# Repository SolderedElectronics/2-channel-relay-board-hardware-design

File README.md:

# 2-channel relay board Hardware Design

## About the Product

|  |
| :----------------------------------------------------------: |
| [Buy 2-channel relay board](https://www.solde.red/333023) |

Did you ever wanted to turn on and off a device that needs large current or voltage? Whether operating on DC or AC, a relay is what you need. A relay is actually an electronic switch that is activated by a signal we send from a Dasduino or Arduino. This module further simplifies the whole process because it contains everything you need for the relay to work, and you just have to connect it to the microcontroller and power supply. You don’t have to think about voltages and currents, insulation between high and low voltage or grounding, everything is already taken care of on the board. This product has 2 relays.

---

## Repository Contents

This repository contains all design files for 2-channel relay board, organized as follows:

- **`CAD` folder**: Contains KiCAD design files, including:
  - Schematics
  - PCB layout
  - Panel PCB layout
  - Source 3D files in Fusion360, if any
  - All files are sorted by version with a detailed change log.
- **`OUTPUTS` folder**: Includes all production-ready files, such as:
  - Bill of Materials (BOM) and interactive BOM (iBOM)
  - PDF versions of schematics
  - 3D `.step` file of the board
  - 3D-printable models
  - Gerber files for PCB manufacturing
  - Image of the pinout of the board
  - Product image
  - Compliance, legal and generic sales documents

Refer to the `Change Log` in the CAD folder for details about updates between versions.

---

## Learn More About the Product

Beyond the repository, explore the following resources:

### Soldered Verify

The **Soldered Verify** system ensures every board you purchase from Soldered is fully functional. It also provides access to exclusive test data for your product. To get started, find the unique Soldered Verify ID on your product's packaging and enter the ID on the [Soldered Verify page](https://soldered.com/verify/) to access test results and additional product details.

### Soldered Community

Soldered Community is your go-to place for technical support. Our engineers track and answer all questions posted there, and it’s a great space for the maker community. Get answers to your questions and solutions for your challenges at [Soldered Community](https://soldered.com/community).

### solde.red

solde.red is an ultimate URL shortener and information hub. Access it by typing solde.red/ followed by your product SKU, e.g., [solde.red/333000](https://solde.red/333000), to find getting-started guides, datasheets, open-source hardware and software files, certifications, images, pinouts, and more. Read more about the shortener [here](https://solde.red/info/).

---

## Contributing

Contributions are welcome! Here’s how you can get involved:

- Submit pull requests to enhance the design or fix issues.
- Report bugs or problems by opening an issue.

We encourage community collaboration to make this product even better.

---

## About Soldered

[Soldered for Makers](https://soldered.com) specializes in designing and manufacturing electronic products tailored for enthusiasts, ranging from hobbyists to professionals. Our portfolio includes electronic boards, sensors, and actuators that are widely utilized in fields such as microelectronics, mechatronics, robotics, programming, and IoT. Every product we offer is designed in-house and built upon open-source hardware and software platforms. Proudly certified and manufactured within the European Union, our catalog likely includes the product you need for your project.

We complement these products with comprehensive tutorials and manuals, product descriptions, schematics, programming codes, and project examples. Our round-the-clock [customer and technical support](https://soldered.com/community) is available for all our products, irrespective of the sales channel. Soldered’s success and services reflect our maker community’s unwavering [trust](https://www.trustpilot.com/review/soldered.com), for which we are deeply grateful. Join our community and create using Soldered products.

---

## License

All Soldered open-source hardware (OSH) is under The TAPR Open Hardware License. Read more in the LICENSE file located in this repository.

**Disclaimer:**

No warranty - all designs in this repository are distributed in the hope that they will be useful, but without any warranty. They are provided "AS IS", therefore without warranty of any kind, either expressed or implied. The entire quality and performance of what you do with the contents of this repository are your responsibility. In no event Soldered Electronics will be liable for your damages, or losses, including any general, special, incidental, or consequential damage arising out of the use or inability to use the contents of this repository. 

---

## Have fun!

Thank you for your support from your fellow makers at Soldered Electronics.

Happy Making!

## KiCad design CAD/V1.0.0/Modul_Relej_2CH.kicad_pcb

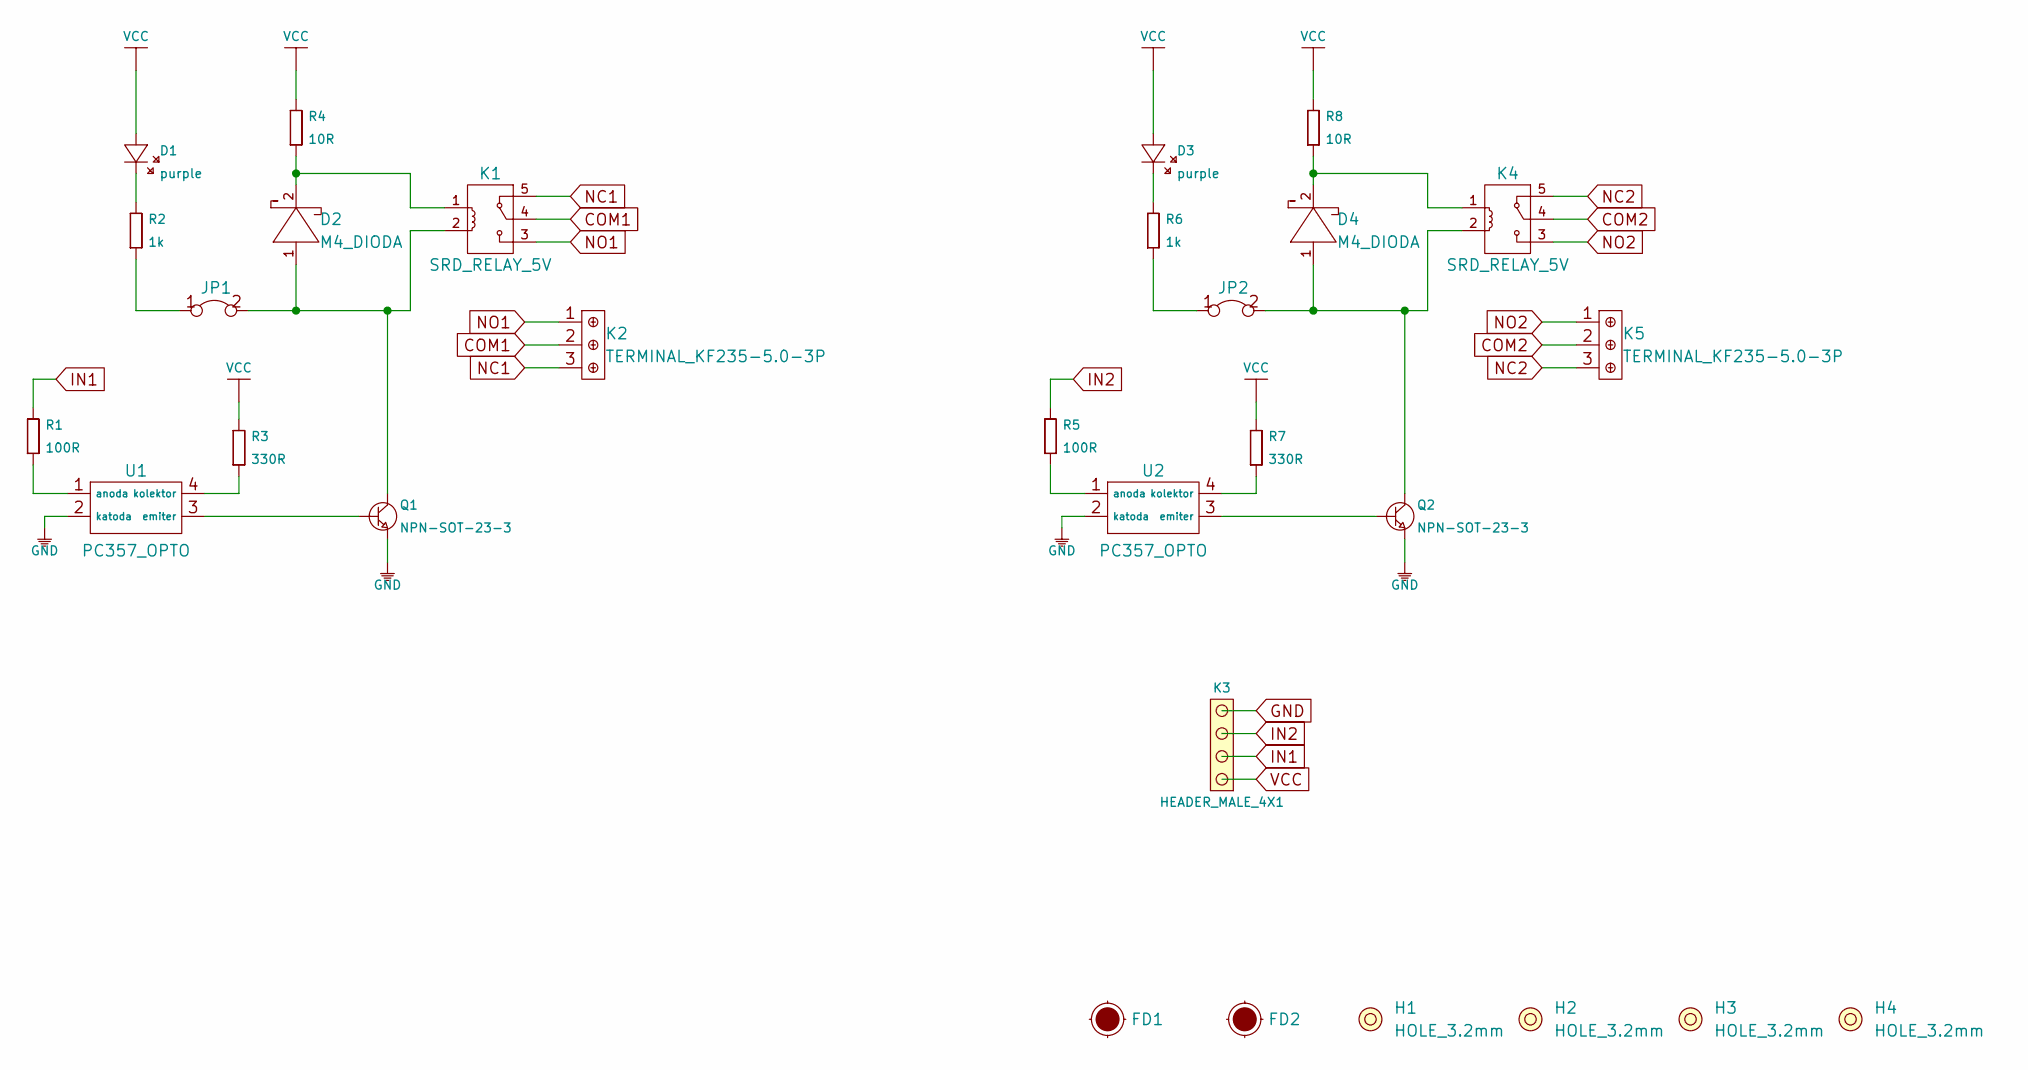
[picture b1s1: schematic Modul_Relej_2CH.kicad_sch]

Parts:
D1, D3: purple; 0402LED
D2, D4: M4_DIODA
FD1, FD2: Fiducial_Stencil; FIDUCIAL_1MM_PASTE
H1, H2, H3, H4: HOLE_3.2mm
JP1, JP2: SMD-JUMPER-CONNECTED_TRACE_NOSLODERMASK
K1, K4: SRD_RELAY_5V
K2, K5: TERMINAL_KF235-5.0-3P
K3: HEADER_MALE_4X1
Q1, Q2: NPN-SOT-23-3; SOT-23-3
R1, R5: 100R; 0603R
R2, R6: 1k; 0402R
R3, R7: 330R; 0603R
R4, R8: 10R; 0603R
U1, U2: PC357_OPTO

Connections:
COM1: K1.4, K2.2
COM2: K4.4, K5.2
GND: K3.4, Q1.2 (E), Q2.2 (E), U1.2 (katoda), U2.2 (katoda)
IN1: K3.2, R1.2
IN2: K3.3, R5.2
NC1: K1.5, K2.3
NC2: K4.5, K5.3
NO1: K1.3, K2.1
NO2: K4.3, K5.1
unnamed: D1.2 (K), R2.2
unnamed: D2.1 (A), JP1.2, K1.2, Q1.3 (C)
unnamed: D2.2 (K), K1.1, R4.1
unnamed: D3.2 (K), R6.2
unnamed: D4.1 (A), JP2.2, K4.2, Q2.3 (C)
unnamed: D4.2 (K), K4.1, R8.1
unnamed: Q1.1 (B), U1.3 (emiter)
unnamed: Q2.1 (B), U2.3 (emiter)
unnamed: R1.1, U1.1 (anoda)
unnamed: JP1.1, R2.1
unnamed: R3.1, U1.4 (kolektor)
unnamed: R5.1, U2.1 (anoda)
unnamed: JP2.1, R6.1
unnamed: R7.1, U2.4 (kolektor)
VCC: D1.1 (A), D3.1 (A), K3.1, R3.2, R4.2, R7.2, R8.2

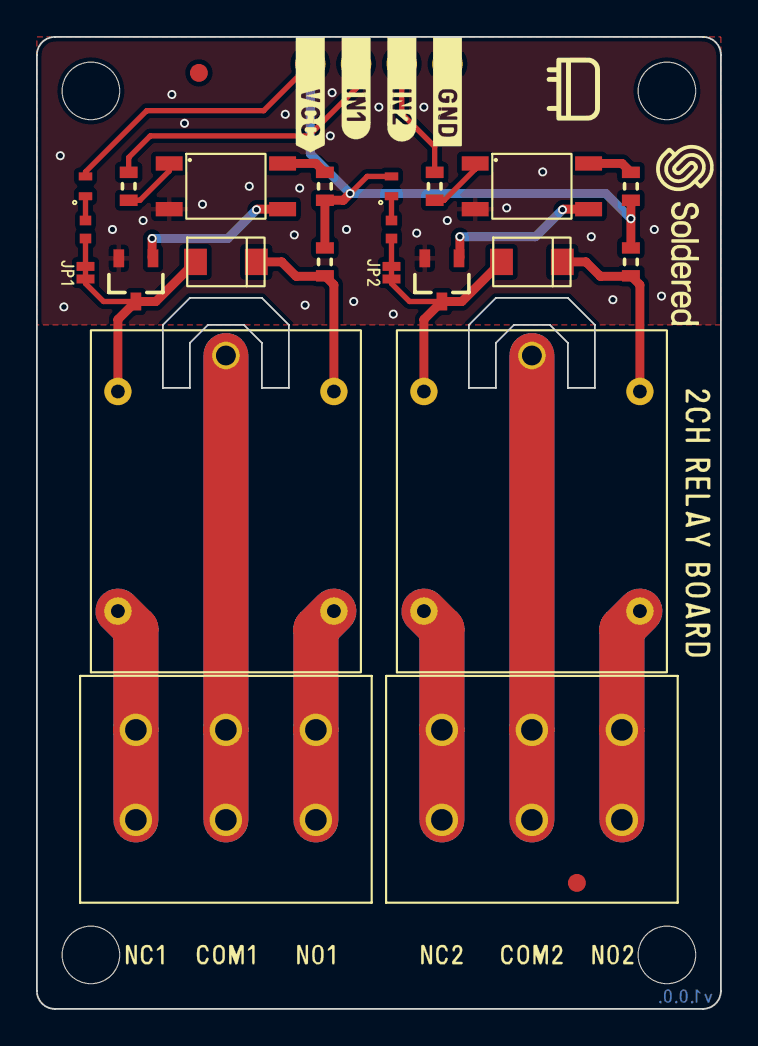
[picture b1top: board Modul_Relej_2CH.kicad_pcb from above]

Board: 2 copper layers, 38.0 x 54.0 mm, 29 parts (0 on the bottom side), 24 nets.

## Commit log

2022-08-06 Updating open source files.
